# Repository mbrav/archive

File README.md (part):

<h1>api_final</h1>
<p>api final</p>
<h2>Описание проекта: README.md</h2>
<p>Выполненный проект должен сопровождаться описанием.</p>
<ul>
<li>[ ] <strong>Описание</strong>. Что это за проект, какую задачу он решает, в чём его польза;</li>
<li>[ ] <strong>Установка</strong>. Как развернуть проект на локальной машине;</li>
<li>[ ] <strong>Примеры</strong>. Некоторые примеры запросов к API.</li>
</ul>
<h1>api_yatube</h1>
<p>api_yatube</p>
<h1>asciify</h1>
<p>An image uploader that converts colored images into ASCII art</p>
<h3>Instructions</h3>
<ol>
<li>Run <code>npm install</code></li>
<li>Serve <code>node app.js</code></li>
<li>Go to <code>localhost:3000</code> on your browser</li>
</ol>
<h3>Requirements</h3>
<p>The <code>jp2a</code> bash command must be installed on the system</p>
<h1>Extensions of Bias</h1>
<p>A new media art installation connected to the Internet through a Twitter API. A speculation on how media technology is actively shaping our increasingly biased human natures.</p>
<h1>Circularis</h1>
<p>A project that manifests the aesthetics of generative music patterns through the use of Euclidean geometries and mathematical sequences.</p>
<h2>Contexts</h2>
<p><a href="https://aeon.co/essays/soon-we-will-see-chrono-attached-to-every-form-of-medicine">Life in Circadia</a> by Jessa Gamble</p>
<h1>Code2-SP16</h1>
<h2><a href="https://mbrav.github.io/archive/Code2-SP16/">Link to Gallery</a></h2>
<p>Code from Code 2 class at Parsons BFADT</p>
<p><strong>Instructor</strong>: <a href="https://github.com/whoisbma">Bryan Ma</a></p>
<p>Spring 2016</p>
<h1>DataSeek</h1>
<p>Exploring the undefined boundaries of rational and irrational data</p>
<h1>Digital Archeology</h1>
<p>PUDT 3000 Final<br />
May 2017</p>
<h2>Narrative</h2>
<h3>Chapter I: The Cosmic Present-Past</h3>
<p>Whenever we take a glimpse at the night sky, most of us rarely realize that what we are looking at--is history. Whatever we see in the night sky, is a collection of photons that have traveled for thousands and millions of years from their point of origin. The photons coming from Alpha Centauri for example--our closest neighboring stellar system--is already 4.3 years old by the time it reaches our telescopes. When we look at the center of our galaxy, we see light that is 27,000 years old. When we observe Andromeda, our neighboring galaxy, we see light that is 2.5 million years old. Our night sky is filled with the cosmic past, and the gigabytes of data collected by our telescopes. This data has yet to be 'excavated' and reveal a cosmic secret lurking among the data. The sky, can be considered an opaque sediment through which the universe's timeline can be observed. Just by looking at the sky, we become archeologists--engaged in the excavation of the past.</p>
<h3>Chapter II: Primeval Ocean</h3>
<p>Before the cosmos gained the ability to host any sense of history, it resembled a turbulent and chaotic ocean. Nothing made sense in the beginning and there was little space for history. But as time unfolded, structure started to prevail--out of what initially was meaningless and unstructured chaos.</p>
<p>These are a few artifacts that are part of human history which emerged out of their chaotic background.</p>
<h3>Chapter III: Creation of Meaning</h3>
<p>As artifacts become introduced in human history, so is meaning. Objects are valued for their inner qualities and this is what makes history itself meaningful. Each historic artifact possesses its own inner world. It is therefore up to the excavators to choose which tools to use in order to excavate an artifact's past.</p>
<p>But are all tools able to reveal the meaningfulness of an artifact? Can excavation tools account all meaningfulness of its objects, or is there something that excavation tools omit?</p>
<p>Zoom into the artifacts using the MOUSE WHEEL to reveal their inner world.</p>
<h3>Chapter IV: Digitization</h3>
<p>Today, digitization has become the current tool for excavating and revealing the past. By taking radio-telescope readings of the night sky, 3D scans of ancient Egyptian statues along with carbon dating techniques--humans engage in a excavation process that transforms every form of history, into a digitized past--a collection of data.</p>
<p>Data is the holy grail of ordering chaos and transforming it into order. If this is the current trend in archeology, then what does it do to the value of the artifacts?</p>
<h3>Chapter V: Anthropic Artifacts</h3>
<p>When we take a look at archaeologic artifacts, how do we want to treat and consider them? Should we stop digitizing the past, and learn how to appreciate it as something that is beyond mere information, but that of eternal value, humanistic, and infinite? Should we return to worshiping Pharaohs like Ancient Egyptians did, or Egyptians did Zeus, or Romans did Jupiter? Could digitizing the past be the most logical and obvious thing to do?</p>
<h3>Chapter VI: The End</h3>
<p>Take a moment to enjoy these digitized artifacts. Some of these would probably disintegrate after a few millions of years, but maybe their digital replica's would exist for longer. </p>
<h2>Todo</h2>
<h3>General</h3>
<ul>
<li>[x] Draft a Narrative</li>
<li>[x] Get the text captions or speech working</li>
<li>[x] Include the narrative as text or speech</li>
<li>[x] Finish project Description</li>
<li>[x] Make a project title screen, name, date, etc.</li>
<li>[x] Polish Attract Mode</li>
<li>[ ] Finish scenes</li>
<li>[x] Scene 1<ul>
<li>[x] narrative</li>
</ul>
</li>
<li>[x] Scene 2<ul>
<li>[x] narrative</li>
</ul>
</li>
<li>[x] Scene 3<ul>
<li>[x] narrative</li>
</ul>
</li>
<li>[x] Scene 4<ul>
<li>[x] narrative</li>
</ul>
</li>
<li>[x] Scene 5<ul>
<li>[ ] narrative</li>
</ul>
</li>
<li>[x] Scene 6<ul>
<li>[ ] narrative</li>
</ul>
</li>
<li>[ ] Scene 7<ul>
<li>[ ] narrative</li>
</ul>
</li>
<li>[ ] Scene 8<ul>
<li>[ ] narrative</li>
</ul>
</li>
<li>[ ] Scene 9<ul>
<li>[ ] narrative</li>
</ul>
</li>
<li>[ ] Music Setup</li>
<li>[x] Bug Fixing</li>
</ul>
<h3>Visual Stuff and Misc</h3>
<ul>
<li>[ ] Scene transitions</li>
<li>[x] Add new forms of visuals</li>
<li>[ ] Add more 3D models</li>
<li>[ ] Decrease poly count of 3D models if necessary</li>
</ul>
<h3>Other Stuff</h3>
<h2>Endeavour's Guide for the 21st Century</h2>
<p>A project based on on reviving James Cook's geographic discoveries that where made while he was the captain of <em><a href="https://en.wikipedia.org/wiki/HMS_Endeavour">Endeavour</a></em>. The device is capable of displaying the direction it is directed by using three 7 segment displays.</p>
<h3>Showcase</h3>
<p><a href="https://youtu.be/tzNWS7Lbi3c">The Endeavour Test</a> - YouTube video</p>
<p><a href="https://i.imgur.com/okikHWv.jpg">Project Plan</a> - Sketch</p>
<h3>Functions</h3>
<ul>
<li>[x] have an effective segment display driver</li>
<li>[x] shows the heading direction of the magnetometer</li>
<li>[ ] have four functional modes</li>
<li>[x] heading mode</li>
<li>[ ] compass mode</li>
<li>[x] direct mode  </li>
<li>[x] save mode  </li>
<li>[ ] make it low powered to allow the use with batteries.</li>
<li>[ ] designed case</li>
</ul>
<h1>EvictionCity</h1>
<p>A visualization of New York metropolitan area home evictions, gentrification, policing of neighborhoods and other social issues which are constitutive to the social antagonisms that inevitably arise under capitalism.</p>
<ul>
<li>Using <a href="https://threejs.org/">three.js JavaScript 3D Library</a></li>
<li>NYC Open Data <a href="https://data.cityofnewyork.us/City-Government/Evictions/6z8x-wfk4/data">Evictions Dataset</a><ol>
<li>Raw <a href="https://raw.githubusercontent.com/mbrav/EvictionCity/master/js/data/evictions-raw.js">JSON data</a></li>
<li><a href="http://mbrav.com/archive/EvictionCity/utilities/util02/">Geocoding and formatting utility</a> using <a href="https://locationiq.com/">LocationIQ</a> (previously it was possible to do it with Google API until it <a href="https://youtu.be/byGIZ4QIHOM">became expensive</a>)</li>
<li><a href="https://raw.githubusercontent.com/mbrav/EvictionCity/master/js/data/geocoded-data-partial.js">Formatted data</a></li>
</ol>
</li>
</ul>
<h1>FlowingPagoda</h1>
<p><em>A Pagoda that never stops flowing...</em></p>
<p>This project was made for one of my classes. It consists of a Pagoda that grows as the season pass.</p>
<h3>Running It</h3>
<ol>
<li><a href="https://processing.org/download/">Download</a> Processing</li>
<li>Install The Minim Library</li>
<li><a href="https://github.com/mixania/FlowingPagoda/archive/master.zip">Download</a> The Project</li>
<li>Run the sketch</li>
</ol>
<h3>Philosophic Meaning</h3>
<p>According to the project’s philosophy, the world and everything that constitutes it relies on a constant process of rebirth and decay. Each moment is an experience of an individual mind-state such as a thought, a memory, a feeling or a perception. A mind-state arises, exists, and since it is impermanent, it soon ceases, following which the next mind-state arises. Thus the consciousness of a sentient being can be seen as a continuous series of birth and decay of these mind-states. Regardless, rebirth always remains the most persistent among these processes.</p>
<p>As the Pagoda flows through the seasons, it is aware that a day will come when it will no longer stand. Its existence will someday become annihilated, but only for a finite time. After its fall, the process of its rebirth will follow after…</p>
<p>The inspiration for this project was drawn from the movie called <em>Crouching Tiger, Hidden Dragon</em> (2000) directed by a Chinese director Ang Lee who is well know being the director of <em>Life of Pi</em> (2012).</p>
<h3>Functions</h3>
<ul>
<li>There are 4 changing seasons</li>
<li>There are 4 different particles that constantly fall</li>
<li>Bamboos that have different stages of growth</li>
<li>Floating Clouds</li>
<li>The Pagoda grows every year</li>
</ul>
<h3>Planned Additions</h3>
<ul>
<li>Create a process of decay of the Pagoda</li>
<li>Create a Chinese dragon that comes every Chinese New Year</li>
<li>Add wind</li>
<li>Add rain</li>
</ul>
<h3>Stages</h3>

<p>Spring</p>

<p>Summer</p>

<p>Fall</p>

<p>Winter</p>
<h1>backend_community_homework</h1>
<p></p>
<h1>backend_community_homework</h1>
<p></p>
<h1>hw04_tests</h1>
<p></p>
<h1>hw05_final</h1>
<p></p>
<ul>
<li>Неправильно сгруппированы импорты. Посмотри, как это рекомендуется делать в pep8 (порядок групп, разделение пустыми строками и т.д.) Еще можно использовать библиотеку <code>isort</code>. Вот есть <a href="https://simpleisbetterthancomplex.com/packages/2016/10/08/isort.html">статья по настройке</a>. Стоит проверить и поправить по всему проекту<ul>
<li><code>isort . --recursive --check-only</code></li>
<li><code>isort . --recursive</code></li>
</ul>
</li>
</ul>
<p>To dump data:
<code>python manage.py dumpdata app.model_name --indent 4 &gt; fixtures/file_name.json</code></p>
<p>To load data:
<code>python manage.py loaddata fixtures/model_name.json --app app.model_name</code></p>
<h1>hw_python_oop</h1>
<p>Sprint 2. Итоговый проект.</p>
<h1>infORM alpha2</h1>
<p>A Physical Computing and Object Relational Mapping tool</p>
<p><a href="https://vimeo.com/161095259">Video</a> of the project</p>
<p>Project's intent <a href="https://mbrav.github.io/archive/infORM/ProjectIntent.pdf">PDF</a></p>
<h2>Instructions</h2>
<p>add your serial port in <em>script.js</em> on the following line:</p>
<p><code>// connect to Serial
serial.open("/dev/cu.usbmodem819431");</code></p>
<p>if you know what you are doing then do...</p>
<p><code>node node/startserver.js</code></p>
<p>if the server does not start, npm dependencies must be install first</p>
<h2>Technologies used</h2>
<ul>
<li>Software<ul>
<li>A node.js server</li>
<li>p5.js JavaScript library</li>
<li>d3.js JavaScript library</li>
<li>JSON</li>
</ul>
</li>
<li>Hardware<ul>
<li>Teensy 3.1 running at 120 MHz (an Arduino Uno might not have enough space or power)</li>
<li>MPU-6050 Accelerometer</li>
<li>HMC5883 Magnetometer</li>
</ul>
</li>
<li>Arduino Libraries<ul>
<li>I2C Library</li>
<li><a href="https://github.com/bblanchon/ArduinoJson">ArduinoJson</a> - An elegant and efficient JSON library for embedded systems.</li>
<li>Adafruit's <a href="https://github.com/adafruit/Adafruit_Sensor">Sensor Library</a></li>
<li>Adafruit's <a href="https://github.com/adafruit/Adafruit_HMC5883_Unified">HMC5883L Library</a></li>
</ul>
</li>
</ul>
<h2>Changes</h2>
<p><strong>alpha2</strong> - March 31, 2016</p>
<ul>
<li>Implemented MPU-6050's temperature readings</li>
<li>Added the HMC5883 magnetometer to the project</li>
<li>Added magnetometer reads</li>
<li>Added different event triggers for each of the type of readings</li>
<li>Improved the calculation of <em>event significance</em> thanks to the added sensors</li>
</ul>
<p><strong>alpha</strong> - March 28, 2016</p>
<ul>
<li>First release</li>
</ul>
<h1>Infrastructural Utopia Tower (2016)</h1>
<p><strong>A <a href="https://vimeo.com/166409996">Video</a> of the Installation</strong></p>
<h2>Abstract</h2>
<p><em>Infrastructural Utopia Tower</em> is an art installation that emphasizes on the way our modern society has become reliant on infrastructures and automated systems. For a modern human, infrastructure is second nature. Without infrastructure, a human would think he/she had been placed in the wilderness. Us humans, attempt to apply infrastructures almost everywhere while the technological advances only aid this process.</p>
<p>Infrastructure is meant to be built in technological environments. We are affected by it, most of the time without even noticing; hundreds of wires pass through walls, dozens of pipes are laid beneath us, and an unknown number of radio frequencies pass through our bodies. All this illustrates infrastructure’s overwhelming presence, yet, it is cleverly engineered to remain unnoticed. We have the privilege to blindly use the word “working” to describe the thousands of operations that infrastructures perform on a daily basis. This however, is a burden as much as it is considered to be a privilege.
<em>Infrastructural Utopia Tower</em> also emphasizes on government surveillance. Surveillance however, is not made possible without it's underlying framework - infrastructure. When something becomes infrastructuralized, one should not wonder why it can be exploited for someone else's advantage. It is a system designed to remain hidden to its intended user, and nevertheless remain manipulable. Combating surveilance becomes ineffective if one does not realize the implications of its underlying framework on top of which it is built. Infrastructure by definition is meant to be controlled and manipulated, this aspect is frequently overlooked since the root in the word infrastructure, <em>infra</em>  - means closed. The technologies we use on a daily basis is perfect example of how hidden technologies can abstract their intended function.</p>
<p>“Infrastructuralize everything” - is a slogan that is subconsciously ingrained in almost every modern human being. It is a process that has to welcome reflection on our part since the perplexities that arise from it, might not always be apparent. <em>Infrastructural Utopia Tower</em> is an infrastructure, the way it was built reflects this aspect. The way it was realized however, is unlike its intended utopian model. It was meant to stand like its 3D model, manifesting the ideals that have had the potential to be realized. This realization did not happen, and the existence of the ideal did not go beyond a 3D model on an LCD screen. What has been realized however, is an anti-utopian application of infrastructure within the tower. The structure transformed into a breeding ground for humankind to infrastructialize as much estate that nature can provide. The outcome is an anti-utopian looking tower that reflects this human characteristic.</p>
<p>The piece features a Wi-Fi spot that sniffs the user data as he/she browses the internet. This serves as a metaphor that illustrates infrastructure's constant connectedness. The tower’s intention is not to hide the infrastructure away from the user, but show its overwhelming presence, authority, and control. An aspect that infrastructures do not have the possibility to show since they remain constantly hidden.</p>
<p>The tower was meant to proclaim digital freedom, an important tool for maintaining a free democratic society in our present. But digital technologies like the internet, are arguably, one of the most manipulable infrastructures that humankind has every built. Today like never before, someone can control the outcome of something that is located on the other side of the globe, or know everything about the individuals that surround him. We are all part of a grid of infrastructures that provide us with resources, commodities, and sustainable living conditions. Many infrastructures also rely on other infrastructures which translates into us being part of the infrastructural grid as well. Even in the most remote places on Earth, infrastructures consist of satellites that fly above our heads. It sounds more literal than it might appear, but when it comes to infrastructures, humans are never in “offline” mode.</p>
<p>The question that has to be asked is whether infrastructures can be used as means for maintaining freedom. Is there a point where freedom can become instrastructialized given the increase in our reliance on technologies? What is the balance between what should be inrastructuralized, and what should not? If our living conditions can be easily provided by infrastructured means, can freedom eventually be “served” like tap water? Once infrastructures become tools for providing human dependencies in very abstracted ways, would human beings not be blind enough to notice this malicious process? If infrastructures are meant to remain so unnoticeable, what is the truth that they hide? These are questions that must be made by a technologically advancing civilization, especially by its citizens.</p>
<h3>Hardware and Technologies Used</h3>
<ul>
<li>Arduino</li>
<li>openFrameworks running on the Raspberry Pi 3</li>
<li>Serial communication</li>
<li>180 APA102 LED Strips
&lt;&lt;&lt;&lt;&lt;&lt;&lt; HEAD
&lt;&lt;&lt;&lt;&lt;&lt;&lt; HEAD</li>
</ul>
<h1>api_final</h1>
<p>api final</p>
<h2>Описание проекта: README.md</h2>
<p>Выполненный проект должен сопровождаться описанием.</p>
<ul>
<li>[ ] <strong>Описание</strong>. Что это за проект, какую задачу он решает, в чём его польза;</li>
<li>[ ] <strong>Установка</strong>. Как развернуть проект на локальной машине;</li>
<li>[ ] <strong>Примеры</strong>. Некоторые примеры запросов к API.</li>
</ul>
<h1>api_yatube</h1>
<p>api_yatube</p>
<h1>asciify</h1>
<p>An image uploader that converts colored images into ASCII art</p>
<h3>Instructions</h3>
<ol>
<li>Run <code>npm install</code></li>
<li>Serve <code>node app.js</code></li>
<li>Go to <code>localhost:3000</code> on your browser</li>
</ol>
<h3>Requirements</h3>
<p>The <code>jp2a</code> bash command must be installed on the system</p>
<h1>Extensions of Bias</h1>
<p>A new media art installation connected to the Internet through a Twitter API. A speculation on how media technology is actively shaping our increasingly biased human natures.</p>
<h1>Circularis</h1>
<p>A project that manifests the aesthetics of generative music patterns through the use of Euclidean geometries and mathematical sequences.</p>
<h2>Contexts</h2>
<p><a href="https://aeon.co/essays/soon-we-will-see-chrono-attached-to-every-form-of-medicine">Life in Circadia</a> by Jessa Gamble</p>
<h1>Code2-SP16</h1>
<p>Code from Code 2 class at Parsons BFADT</p>
<p><strong>Instructor</strong>: <a href="https://github.com/whoisbma">Bryan Ma</a></p>
<p>Spring 2016</p>
<h1>DataSeek</h1>
<p>Exploring the undefined boundaries of rational and irrational data</p>
<h1>Digital Archeology</h1>
<p>PUDT 3000 Final<br />
May 2017</p>
<h2>Narrative</h2>
<h3>Chapter I: The Cosmic Present-Past</h3>
<p>Whenever we take a glimpse at the night sky, most of us rarely realize that what we are looking at--is history. Whatever we see in the night sky, is a collection of photons that have traveled for thousands and millions of years from their point of origin. The photons coming from Alpha Centauri for example--our closest neighboring stellar system--is already 4.3 years old by the time it reaches our telescopes. When we look at the center of our galaxy, we see light that is 27,000 years old. When we observe Andromeda, our neighboring galaxy, we see light that is 2.5 million years old. Our night sky is filled with the cosmic past, and the gigabytes of data collected by our telescopes. This data has yet to be 'excavated' and reveal a cosmic secret lurking among the data. The sky, can be considered an opaque sediment through which the universe's timeline can be observed. Just by looking at the sky, we become archeologists--engaged in the excavation of the past.</p>
<h3>Chapter II: Primeval Ocean</h3>
<p>Before the cosmos gained the ability to host any sense of history, it resembled a turbulent and chaotic ocean. Nothing made sense in the beginning and there was little space for history. But as time unfolded, structure started to prevail--out of what initially was meaningless and unstructured chaos.</p>
<p>These are a few artifacts that are part of human history which emerged out of their chaotic background.</p>
<h3>Chapter III: Creation of Meaning</h3>
<p>As artifacts become introduced in human history, so is meaning. Objects are valued for their inner qualities and this is what makes history itself meaningful. Each historic artifact possesses its own inner world. It is therefore up to the excavators to choose which tools to use in order to excavate an artifact's past.</p>
<p>But are all tools able to reveal the meaningfulness of an artifact? Can excavation tools account all meaningfulness of its objects, or is there something that excavation tools omit?</p>
<p>Zoom into the artifacts using the MOUSE WHEEL to reveal their inner world.</p>
<h3>Chapter IV: Digitization</h3>
<p>Today, digitization has become the current tool for excavating and revealing the past. By taking radio-telescope readings of the night sky, 3D scans of ancient Egyptian statues along with carbon dating techniques--humans engage in a excavation process that transforms every form of history, into a digitized past--a collection of data.</p>
<p>Data is the holy grail of ordering chaos and transforming it into order. If this is the current trend in archeology, then what does it do to the value of the artifacts?</p>
<h3>Chapter V: Anthropic Artifacts</h3>
<p>When we take a look at archaeologic artifacts, how do we want to treat and consider them? Should we stop digitizing the past, and learn how to appreciate it as something that is beyond mere information, but that of eternal value, humanistic, and infinite? Should we return to worshiping Pharaohs like Ancient Egyptians did, or Egyptians did Zeus, or Romans did Jupiter? Could digitizing the past be the most logical and obvious thing to do?</p>
<h3>Chapter VI: The End</h3>
<p>Take a moment to enjoy these digitized artifacts. Some of these would probably disintegrate after a few millions of years, but maybe their digital replica's would exist for longer. </p>
<h2>Todo</h2>
<h3>General</h3>
<ul>
<li>[x] Draft a Narrative</li>
<li>[x] Get the text captions or speech working</li>
<li>[x] Include the narrative as text or speech</li>
<li>[x] Finish project Description</li>
<li>[x] Make a project title screen, name, date, etc.</li>
<li>[x] Polish Attract Mode</li>
<li>[ ] Finish scenes</li>
<li>[x] Scene 1<ul>
<li>[x] narrative</li>
</ul>
</li>
<li>[x] Scene 2<ul>
<li>[x] narrative</li>
</ul>
</li>
<li>[x] Scene 3<ul>
<li>[x] narrative</li>
</ul>
</li>
<li>[x] Scene 4<ul>
<li>[x] narrative</li>
</ul>
</li>
<li>[x] Scene 5<ul>
<li>[ ] narrative</li>
</ul>
</li>
<li>[x] Scene 6<ul>
<li>[ ] narrative</li>
</ul>
</li>
<li>[ ] Scene 7<ul>
<li>[ ] narrative</li>
</ul>
</li>
<li>[ ] Scene 8<ul>
<li>[ ] narrative</li>
</ul>
</li>
<li>[ ] Scene 9<ul>
<li>[ ] narrative</li>
</ul>
</li>
<li>[ ] Music Setup</li>
<li>[x] Bug Fixing</li>
</ul>
<h3>Visual Stuff and Misc</h3>
<ul>
<li>[ ] Scene transitions</li>
<li>[x] Add new forms of visuals</li>
<li>[ ] Add more 3D models</li>
<li>[ ] Decrease poly count of 3D models if necessary</li>
</ul>
<h3>Other Stuff</h3>
<h2>Endeavour's Guide for the 21st Century</h2>
<p>A project based on on reviving James Cook's geographic discoveries that where made while he was the captain of <em><a href="https://en.wikipedia.org/wiki/HMS_Endeavour">Endeavour</a></em>. The device is capable of displaying the direction it is directed by using three 7 segment displays.</p>
<h3>Showcase</h3>
<p><a href="https://youtu.be/tzNWS7Lbi3c">The Endeavour Test</a> - YouTube video</p>
<p><a href="https://i.imgur.com/okikHWv.jpg">Project Plan</a> - Sketch</p>
<h3>Functions</h3>
<ul>
<li>[x] have an effective segment display driver</li>
<li>[x] shows the heading direction of the magnetometer</li>
<li>[ ] have four functional modes</li>
<li>[x] heading mode</li>
<li>[ ] compass mode</li>
<li>[x] direct mode  </li>
<li>[x] save mode  </li>
<li>[ ] make it low powered to allow the use with batteries.</li>
<li>[ ] designed case</li>
</ul>
<h1>EvictionCity</h1>
<p>A visualization of New York metropolitan area home evictions, gentrification, policing of neighborhoods and other social issues which are constitutive to the social antagonisms that inevitably arise under capitalism.</p>
<ul>
<li>Using <a href="https://threejs.org/">three.js JavaScript 3D Library</a></li>
<li>NYC Open Data <a href="https://data.cityofnewyork.us/City-Government/Evictions/6z8x-wfk4/data">Evictions Dataset</a></li>
<li>Raw <a href="https://raw.githubusercontent.com/mbrav/EvictionCity/master/js/data/evictions-raw.js">JSON data</a></li>
<li><a href="http://mbrav.com/EvictionCity/utilities/util02/">Geocoding and formatting utility</a> using <a href="https://locationiq.com/">LocationIQ</a> (previously it was possible to do it with Google API until it <a href="https://youtu.be/byGIZ4QIHOM">became expensive</a>)</li>
<li><a href="https://raw.githubusercontent.com/mbrav/EvictionCity/master/js/data/geocoded-data-partial.js">Formatted data</a></li>
</ul>
<h1>FlowingPagoda</h1>
<p><em>A Pagoda that never stops flowing...</em></p>
<p>This project was made for one of my classes. It consists of a Pagoda that grows as the season pass.</p>
<h3>Running It</h3>
<ol>
<li><a href="https://processing.org/download/">Download</a> Processing</li>
<li>Install The Minim Library</li>
<li><a href="https://github.com/mixania/FlowingPagoda/archive/master.zip">Download</a> The Project</li>
<li>Run the sketch</li>
</ol>
<h3>Philosophic Meaning</h3>
<p>According to the project’s philosophy, the world and everything that constitutes it relies on a constant process of rebirth and decay. Each moment is an experience of an individual mind-state such as a thought, a memory, a feeling or a perception. A mind-state arises, exists, and since it is impermanent, it soon ceases, following which the next mind-state arises. Thus the consciousness of a sentient being can be seen as a continuous series of birth and decay of these mind-states. Regardless, rebirth always remains the most persistent among these processes.</p>
<p>As the Pagoda flows through the seasons, it is aware that a day will come when it will no longer stand. Its existence will someday become annihilated, but only for a finite time. After its fall, the process of its rebirth will follow after…</p>
<p>The inspiration for this project was drawn from the movie called <em>Crouching Tiger, Hidden Dragon</em> (2000) directed by a Chinese director Ang Lee who is well know being the director of <em>Life of Pi</em> (2012).</p>
<h3>Functions</h3>
<ul>
<li>There are 4 changing seasons</li>
<li>There are 4 different particles that constantly fall</li>
<li>Bamboos that have different stages of growth</li>
<li>Floating Clouds</li>
<li>The Pagoda grows every year</li>
</ul>
<h3>Planned Additions</h3>
<ul>
<li>Create a process of decay of the Pagoda</li>
<li>Create a Chinese dragon that comes every Chinese New Year</li>
<li>Add wind</li>
<li>Add rain</li>
</ul>
<h3>Stages</h3>

<p>Spring</p>

<p>Summer</p>

<p>Fall</p>

<p>Winter</p>
<h1>backend_community_homework</h1>
<p></p>
<h1>backend_community_homework</h1>
<p></p>
<h1>hw04_tests</h1>
<p></p>
<h1>hw05_final</h1>
<p></p>
<ul>
<li>Неправильно сгруппированы импорты. Посмотри, как это рекомендуется делать в pep8 (порядок групп, разделение пустыми строками и т.д.) Еще можно использовать библиотеку <code>isort</code>. Вот есть <a href="https://simpleisbetterthancomplex.com/packages/2016/10/08/isort.html">статья по настройке</a>. Стоит проверить и поправить по всему проекту<ul>
<li><code>isort . --recursive --check-only</code></li>
<li><code>isort . --recursive</code></li>
</ul>
</li>
</ul>
<p>To dump data:
<code>python manage.py dumpdata app.model_name --indent 4 &gt; fixtures/file_name.json</code></p>
<p>To load data:
<code>python manage.py loaddata fixtures/model_name.json --app app.model_name</code></p>
<h1>hw_python_oop</h1>
<p>Sprint 2. Итоговый проект.</p>
<h1>infORM alpha2</h1>
<p>A Physical Computing and Object Relational Mapping tool</p>
<p><a href="https://vimeo.com/161095259">Video</a> of the project</p>
<p>Project's intent <a href="https://github.com/mixania/infORM/blob/master/ProjectIntent.pdf">PDF</a></p>
<h2>Instructions</h2>
<p>add your serial port in <em>script.js</em> on the following line:
<code>// connect to Serial
serial.open("/dev/cu.usbmodem819431");</code></p>
<p>if you know what you are doing then do...
<code>node node/startserver.js</code></p>
<p>if the server does not start, npm dependencies must be install first</p>
<h2>Technologies used</h2>
<ul>
<li>Software</li>
<li>A node.js server</li>
<li>p5.js JavaScript library</li>
<li>d3.js JavaScript library</li>
<li>JSON</li>
<li>Hardware</li>
<li>Teensy 3.1 running at 120 MHz (an Arduino Uno might not have enough space or power)</li>
<li>MPU-6050 Accelerometer</li>
<li>HMC5883 Magnetometer</li>
<li>Arduino Libraries</li>
<li>I2C Library</li>
<li><a href="https://github.com/bblanchon/ArduinoJson">ArduinoJson</a> - An elegant and efficient JSON library for embedded systems.</li>
<li>Adafruit's <a href="https://github.com/adafruit/Adafruit_Sensor">Sensor Library</a></li>
<li>Adafruit's <a href="https://github.com/adafruit/Adafruit_HMC5883_Unified">HMC5883L Library</a></li>
</ul>
<h2>Changes</h2>
<p><strong>alpha2</strong> - March 31, 2016
* Implemented MPU-6050's temperature readings
* Added the HMC5883 magnetometer to the project
* Added magnetometer reads
* Added different event triggers for each of the type of readings
* Improved the calculation of <em>event significance</em> thanks to the added sensors</p>
<p><strong>alpha</strong> - March 28, 2016
* First release</p>
<h1>Infrastructural Utopia Tower (2016)</h1>
<p><strong>A <a href="https://vimeo.com/166409996">Video</a> of the Installation</strong></p>
<h2>Abstract</h2>
<p><em>Infrastructural Utopia Tower</em> is an art installation that emphasizes on the way our modern society has become reliant on infrastructures and automated systems. For a modern human, infrastructure is second nature. Without infrastructure, a human would think he/she had been placed in the wilderness. Us humans, attempt to apply infrastructures almost everywhere while the technological advances only aid this process.</p>
<p>Infrastructure is meant to be built in technological environments. We are affected by it, most of the time without even noticing; hundreds of wires pass through walls, dozens of pipes are laid beneath us, and an unknown number of radio frequencies pass through our bodies. All this illustrates infrastructure’s overwhelming presence, yet, it is cleverly engineered to remain unnoticed. We have the privilege to blindly use the word “working” to describe the thousands of operations that infrastructures perform on a daily basis. This however, is a burden as much as it is considered to be a privilege.
<em>Infrastructural Utopia Tower</em> also emphasizes on government surveillance. Surveillance however, is not made possible without it's underlying framework - infrastructure. When something becomes infrastructuralized, one should not wonder why it can be exploited for someone else's advantage. It is a system designed to remain hidden to its intended user, and nevertheless remain manipulable. Combating surveilance becomes ineffective if one does not realize the implications of its underlying framework on top of which it is built. Infrastructure by definition is meant to be controlled and manipulated, this aspect is frequently overlooked since the root in the word infrastructure, <em>infra</em>  - means closed. The technologies we use on a daily basis is perfect example of how hidden technologies can abstract their intended function.</p>
<p>“Infrastructuralize everything” - is a slogan that is subconsciously ingrained in almost every modern human being. It is a process that has to welcome reflection on our part since the perplexities that arise from it, might not always be apparent. <em>Infrastructural Utopia Tower</em> is an infrastructure, the way it was built reflects this aspect. The way it was realized however, is unlike its intended utopian model. It was meant to stand like its 3D model, manifesting the ideals that have had the potential to be realized. This realization did not happen, and the existence of the ideal did not go beyond a 3D model on an LCD screen. What has been realized however, is an anti-utopian application of infrastructure within the tower. The structure transformed into a breeding ground for humankind to infrastructialize as much estate that nature can provide. The outcome is an anti-utopian looking tower that reflects this human characteristic.</p>
<p>The piece features a Wi-Fi spot that sniffs the user data as he/she browses the internet. This serves as a metaphor that illustrates infrastructure's constant connectedness. The tower’s intention is not to hide the infrastructure away from the user, but show its overwhelming presence, authority, and control. An aspect that infrastructures do not have the possibility to show since they remain constantly hidden.</p>
<p>The tower was meant to proclaim digital freedom, an important tool for maintaining a free democratic society in our present. But digital technologies like the internet, are arguably, one of the most manipulable infrastructures that humankind has every built. Today like never before, someone can control the outcome of something that is located on the other side of the globe, or know everything about the individuals that surround him. We are all part of a grid of infrastructures that provide us with resources, commodities, and sustainable living conditions. Many infrastructures also rely on other infrastructures which translates into us being part of the infrastructural grid as well. Even in the most remote places on Earth, infrastructures consist of satellites that fly above our heads. It sounds more literal than it might appear, but when it comes to infrastructures, humans are never in “offline” mode.</p>
<p>The question that has to be asked is whether infrastructures can be used as means for maintaining freedom. Is there a point where freedom can become instrastructialized given the increase in our reliance on technologies? What is the balance between what should be inrastructuralized, and what should not? If our living conditions can be easily provided by infrastructured means, can freedom eventually be “served” like tap water? Once infrastructures become tools for providing human dependencies in very abstracted ways, would human beings not be blind enough to notice this malicious process? If infrastructures are meant to remain so unnoticeable, what is the truth that they hide? These are questions that must be made by a technologically advancing civilization, especially by its citizens.</p>
<h3>Hardware and Technologies Used</h3>
<ul>
<li>Arduino</li>
<li>openFrameworks running on the Raspberry Pi 3</li>
<li>Serial communication</li>
<li>180 APA102 LED Strips</li>
</ul>
<h1>Core Lab: Systems</h1>
<p><strong>Instructors</strong>: Miri Park &amp; Bryan Collinsworth</p>
<p>Fall 2016</p>
<h2>Sketches</h2>
<h3><a href="02/">02</a> - Random Sequence</h3>

<h3><a href="03/">03</a> - Fibonacci Sequence</h3>

<h3><a href="04/">04</a> - Fibonacci Sequence &amp; Composition</h3>

<h3><a href="05/">05</a> - Chaotic Harmony</h3>

<h3><a href="06/">06</a> - Sleep Harmonics I</h3>

<h3><a href="07/">07</a> - Sleep Harmonics II</h3>

<h3><a href="08/">08</a> - Sleep Harmonics III</h3>

<h3><a href="09/">09</a> - Emancipation from Sleep Data</h3>

<h3><a href="10/">10</a> - Sleep Data Abyss</h3>

<h3><a href="11/">11</a> - Sleep Data Abyss II</h3>

<h3><a href="12/">12</a> - Sleep Data Abyss III</h3>

<h3><a href="13/">13</a> - Ice Nine Unleashed</h3>

<h3><a href="14/">14</a> - Green-Ice Resistance</h3>

<h3><a href="15/">15</a> - Post-Ice Condition</h3>

<h3><a href="16/">16</a> - NYC Graffiti Data</h3>

<h3><a href="17/">17</a> - Glitch Outcomes</h3>

<h3><a href="18/">18</a> - n+1 Dimension</h3>

<h3><a href="19/">19</a> - Data Cocoon</h3>

<h3><a href="20/">20</a> - Sound Data Cocoon</h3>

<h3><a href="21/">21</a> - Data Dystopia</h3>

<h3><a href="22/">22</a> - Data Dystopia II</h3>

<h3><a href="23/">23</a> - Sea Shell</h3>

<h3><a href="24/">24</a> - 4D trigonometry</h3>

<h3><a href="25/">25</a> - 4D trigonometry II</h3>

<h3><a href="26/">26</a> - Polygon Planets</h3>

<h3><a href="27/">27</a> - Time Fabric</h3>

<h3><a href="28/">28</a> - Shadows</h3>

<h3><a href="29/">29</a> - WebGL</h3>

<h1>Lab-SP17</h1>
<p>Code from Lab: Collaboration, Parsons BFADT, Spring 2017</p>
<p><strong>Instructor:</strong> Aaron Lehr</p>
<h3><a href="01/">01</a> - terra-form</h3>
<h3><a href="02/">02</a> - museum-visit</h3>
<h3><a href="03/">03</a> - museum-visualization</h3>
<h3><a href="04/">04</a> - ascii</h3>
<h3><a href="https://github.com/mbrav/asciify">05</a> - ASCIIfy</h3>
<h3><a href="06/">06</a> - Web Scraping</h3>
<h3><a href="07/">07  - Midterm</a> - Wiki Faces</h3>
<h1>Lab-SP17</h1>
<p>Code from Lab: Collaboration, Parsons BFADT, Spring 2017</p>
<p><strong>Instructor:</strong> Aaron Lehr</p>
<h3><a href="01/">01</a> - terra-form</h3>
<h3><a href="02/">02</a> - museum-visit</h3>
<h3><a href="03/">03</a> - museum-visualization</h3>
<h3><a href="04/">04</a> - ascii</h3>
<h3><a href="https://github.com/mbrav/asciify">05</a> - ASCIIfy</h3>
<h3><a href="06/">06</a> - Web Scraping</h3>
<h3><a href="07/">07  - Midterm</a> - Wiki Faces</h3>
<p>test# archive
Archive of my old repos</p>
<h1>Multiverse Clockwork</h1>
<p>An openFrameworks project inspired by Clockwork Orange and nihilistic theoretical physics</p>
<p><a href="https://vimeo.com/164663100">Video</a> of the project</p>
<h2>Concept</h2>
<p>For this creative coding project I wanted imitate the animations that were popular at the time when <em>A Clockwork Orange</em> (1971) was created. During that time, computer graphics first started to emerge. I wanted to create an animation that would encompass the aspects of CG if they were to be applied in the <em>A Clockwork Orange</em> movie, but with the inclusion of a few animations that would convey multiverse theory concepts. The translation of a orange circle came out more literal than the translation of the multiverse concept, this turned out to be in parallel with their comprehensibility. The multiverse theory concepts are influenced by Jim Holt’s book <em>Why Does the World Exist?</em>.</p>
<p>The animation starts with the original <em>A Clockwork Orange</em> theme melody which signifies the low complexity of one universe. This part of the animation is very literal. Then as the music progresses into a more progressive form, the animations become more intricate, abstract, and complex. This is an attempt to convey the complexity of multiverse theories which are abstract to our comprehension as are the animations that try to represent them.</p>
<p>The way this coding project was taking its path easily emerged into such a theme and has yielded pretty satisfying results. The code itself is almost 700 lines long which gives it an ironic aspect; it is written in such a fashion that only its creator can understand.This is similar to the way multiverses can be imagined as ideas since we might not be able to comprehend their inner functioning. The way this project was coded should be a challenge for anyone’s understanding.</p>
<h2>Copyright material</h2>
<p>ClockWork Orange - Funeral Of Queen Mary</p>
<p>© A Clockwork Orange</p>
<p>Deadmau5 - Clockwork</p>
<p>© Songbird 2008</p>
<h2>Installation</h2>
<p>First, make sure you are running the <em>Raspbian</em> or <em>NOOBS</em> OS. After you have your Raspberry Pi up and running, make sure <em>pip</em> the python package manager is installed on your Raspberry Pi. If not type the following in Raspberry Pi's terminal.</p>
<p><code>$ sudo apt-get install python-pip</code><br />
Install <a href="http://flask.pocoo.org/">Flask</a> Python microframework
<code>$ sudo pip install flask</code>
Now you are ready to clone the code from GitHub, type the following
<code>$ git clone https://github.com/mixania/rpi-flask.git</code>
Now type the <code>cd</code> command to open the directory
<code>$ cd rpi-flask/</code>
Run the server as <code>sudo</code>(with root privileges)
<code>$ sudo python switch.py</code>
Your server should be running on http://127.0.0.1:80/
</p>
<h2>Description</h2>
<p><em>Stardust Music Composer</em> is an experiment that emphasizes on interactivity and visualization and combining it with music composition. Current Digital Audio Workstation (DAW) software used for music production by professionals, does not incorporate any aspects of interaction outside of the technical realm. This experimental project seeks to add a visual element to the music production process and combine it with an interactive aspect.</p>
<p>The user interacts with the interface by pressing keys that trigger audio loop samples. As the samples play music loops, the user can open a drum machine sequencer and compose a drum pattern and allowing a musical and a visual performance to be produced at the same time.</p>
<p>The visualization is composed of many particles that act like stardust. When there is a peak in the audio levels, a point of gravity is added in the visualization to which all the particles become attracted to. The user can also click on the visualization and interact with the particles. This is perhaps the most important aspect of the music composition that the experiment seeks to emphasize on. Interaction can be just as important as the process of music composition.</p>
<h2>Instructions</h2>
<ol>
<li><a href="https://processing.org/download/">Download</a> Processing</li>
<li>Install The Minim Library using the library manager in Processing</li>
<li>Download this project</li>
<li>Run the sketch by opening any one of the <em>.pde</em> files and clicking <strong>Run</strong></li>
</ol>
<h2>Copyright Material</h2>
<ul>
<li>Audio sample from Miles Davis's <em>Blue In Green</em></li>
</ul>
<h1>TechnelogicalFeudalism</h1>
<p><em>Surveilance from the time when technology was synonymous with art</em></p>
<h2>Description</h2>
<p>Technelogical Feudalism is a experimentation that explores the ways class societies where controlled before the advent of modern manipulable infrastructures. The mode of control that is explored in this particular experimentation is religion. This peace does not critique religion as a system of believe, rather, the way it is applied in societies.</p>
<p>During he Medieval Ages, which where notorious for various pandemics such such as the Black Death, humanity relied on religion as its biggest hope. Today we see how people rely on technology the same way religions where relied on during medieval ages. Technology could bring us increased life expectancy, an increase quality of life, and happiness - the same way religions where believe to. But when humanity relies on something, there is always room for exploitation, especially if that reliance is appealing to the masses.</p>
<p>This experimentation divides the user into two groups, the Noble, and the Peasant. This is an experience that is intended for multiple users where some interact with the experimentation, and other users watch how they interact on the black canvas. The Noble is able to track the mouse portion and clicks. Multiple windows can be opened to simulate the interaction between multiple people.</p>
<p>The peasant side is given an opportunity to accept religion and is given an semi-interactive environment. On the other side of the user, there is a person who looks at his actions. The very fact that he can monitor the actions of the Peasant, means that he is more manipulable. Religion here, is served as a form of entertainment that also translated into a form of surveilance and establishments of control.</p>
<h2>Navigation</h2>
<h4>User chooses his class</h4>

<h4>Peasant's screen</h4>

<h4>You become noble by claiming an oath</h4>

<h4>The noble can now spy on peasants</h4>

<h1>yogabot</h1>
<p>An instagram bot with a set of methodologies that attempt to steal SMM leads from competitor businesses. </p>
<h2>Todo fixes</h2>
<ul>
<li>[x] Interact with feed function <code>feedinteract()</code></li>
<li>[ ] Interact with likers/folowers of competitors </li>
<li>[ ] Follow function <code>follow()</code></li>
<li>[ ] Unfollow function <code>unfollow()</code>s</li>
</ul>
<p>=======</p>
<h1>New York Data City</h1>
<p>NYDC is a project that explores the conventional aspects of data representation. Data visualization is frequently used to convey information using highly abstracted visual and vocabulary symbols. In some cases, humans can only interpret data only because a symbolic reference is provide along the visualization.</p>
<p>Data visualization can be politicized and manipulated through symbols. It can force the viewer to interpret the data in a very intentional and particular way. The semantic symbols in a data visualization, can sometimes become the most significant factor to dictate the viewer’s interpretation of the data. People frequently use terms like “let data speak for itself” as a substitute to meaningful informational representation. Data can be represented in more abstract forms that may convey its inherit nature and its meaningfulness.</p>
<p><a href="https://mbrav.github.io/nydc/01/index.html">Visual 01</a> - NYC Farmer Markets (<a href="https://data.cityofnewyork.us/Health/New-York-City-Farmers-Markets/j8gx-kc43/data">data source</a>)</p>
<p><a href="https://mbrav.github.io/nydc/02/index.html">Visual 02</a> - NYC Water Complaints (<a href="https://data.cityofnewyork.us/Environment/Water-Quality-complaints/qfe3-6dkn/data">data source</a>)</p>
<p><a href="https://mbrav.github.io/nydc/03/index.html">Visual 03</a> - NYC Greenthumb Community Gardens (<a href="https://data.cityofnewyork.us/Environment/NYC-Greenthumb-Community-Gardens/ajxm-kzmj">data source</a>)</p>
<p><a href="https://mbrav.github.io/nydc/04/index.html">Visual 04</a> - NYC Cool Roof Buildings (<a href="https://data.cityofnewyork.us/Environment/NYC-Cool-Roofs-Buildings/uuxn-wzxe/data">data source</a>)</p>
<p><a href="https://mbrav.github.io/nydc/05/index.html">Visual 05</a> - NYC Food Scrap Drop Of Sites (<a href="https://data.cityofnewyork.us/Environment/Food-Scrap-Drop-Off-Sites/rmmq-46n5/data">data source</a>)</p>
<p><a href="https://mbrav.github.io/nydc/06/index.html">Visual 06</a> - NYC Projects in Construction (<a href="https://nycopendata.socrata.com/Housing-Development/Projects-in-Construction-Map/dzgh-ja44/data">data source</a>)</p>
<p><a href="https://mbrav.github.io/nydc/07/index.html">Visual 07</a> - .nyc Domain Registration by Zip Code (<a href="https://data.cityofnewyork.us/Business/-nyc-Domain-Registrations-by-Zip-Code/ymvu-4x4s/data">data source</a>)</p>
<p><a href="https://mbrav.github.io/nydc/08/index.html">Visual 08</a> - NYC Approved Wholesale Markets (<a href="https://data.cityofnewyork.us/Business/Approved-registrants-in-the-wholesale-markets/sapz-4gsi">data source</a>)</p>
<p><a href="https://mbrav.github.io/nydc/09/index.html">Visual 09</a> - NYC Public Recycling Bins (<a href="https://data.cityofnewyork.us/Environment/Public-Recycling-Bins/sxx4-xhzg/data">data source</a>)</p>
<p><a href="https://mbrav.github.io/nydc/10/index.html">Visual 10</a> - NYC Health and Hospital Corporation (HHC) Facilities (<a href="https://data.cityofnewyork.us/Health/NYC-Health-and-Hospitals-Corporation-Facilities/ymhw-9cz9/data">data source</a>)</p>
<p><a href="https://mbrav.github.io/nydc/11/index.html">Visual 11</a> - NYDC Combined visualization</p>

<h2>Instructions</h2>
<p>Use the <code>W</code>,<code>A</code>,<code>S</code>, and<code>D</code> keys to navigate forwards, left , back, and right.</p>
<p>Use <code>Q</code> and <code>E</code> to rotate the camera.</p>
<p>Use the mouse to stir the direction.</p>
<p><strong>Does not yet support mobile device movement</strong>  </p>
<h2>Process</h2>
<p><a href="https://github.com/mbrav/nydc/tree/master/utils">utils</a> - a set of utilities that where used for geocoding and parsing the data.</p>
<p>The converted data can be <a href="https://github.com/mbrav/nydc/tree/master/data">found here</a> as .js files.</p>
<p>Some of the parts of this project are based on <a href="https://github.com/mbrav/nydc/tree/master/graffiti">graffiti-data</a>.</p>
<p>Geocoding <a href="https://youtu.be/WlM96wBV5nU">NYC Greenthumb Community Gardens</a> using Google's API</p>
<p>Geocoding <a href="https://youtu.be/byGIZ4QIHOM">NYC Farmer Markets</a> using Google's API</p>
<h3>Made with</h3>
<ul>
<li><a href="https://threejs.org/">three.js</a> and WebGL</li>
<li><a href="https://nycopendata.socrata.com/">NYC Open Data</a> </li>
</ul>
<h2>Influence</h2>
<p>Cao Fei's - <a href="https://www.youtube.com/watch?v=9MhfATPZA0g">RMB City</a></p>
<p>Cao Fei's - <a href="https://www.youtube.com/watch?v=5vcR7OkzHkI">China Tracy</a></p>
<blockquote>
<h1>&gt;&gt;&gt;&gt;&gt;&gt; nydc/master</h1>
</blockquote>
<h1>KOS-Scripts</h1>
<p>Various scripts using the <a href="https://github.com/KSP-KOS/KOS">kOS mod</a> for <a href="https://store.steampowered.com/app/220200/Kerbal_Space_Program/">KSP</a> </p>
<blockquote>
<blockquote>
<blockquote>
<blockquote>
<blockquote>
<blockquote>
<blockquote>
<p>KOS-Scripts/master</p>
</blockquote>
</blockquote>
</blockquote>
</blockquote>
</blockquote>
</blockquote>
</blockquote>
<h1>Core Lab: Systems</h1>
<p><strong>Instructors</strong>: Miri Park &amp; Bryan Collinsworth</p>
<p>Fall 2016</p>
<h2>Sketches</h2>
<h3><a href="https://mbrav.github.io/archive/Lab-FA16/02/">02</a> - Random Sequence</h3>

<h3><a href="https://mbrav.github.io/archive/Lab-FA16/03/">03</a> - Fibonacci Sequence</h3>

<h3><a href="https://mbrav.github.io/archive/Lab-FA16/04/">04</a> - Fibonacci Sequence &amp; Composition</h3>

<h3><a href="https://mbrav.github.io/archive/Lab-FA16/05/">05</a> - Chaotic Harmony</h3>

<h3><a href="https://mbrav.github.io/archive/Lab-FA16/06/">06</a> - Sleep Harmonics I</h3>

<h3><a href="https://mbrav.github.io/archive/Lab-FA16/07/">07</a> - Sleep Harmonics II</h3>

<h3><a href="https://mbrav.github.io/archive/Lab-FA16/08/">08</a> - Sleep Harmonics III</h3>

<h3><a href="https://mbrav.github.io/archive/Lab-FA16/09/">09</a> - Emancipation from Sleep Data</h3>

<h3><a href="https://mbrav.github.io/archive/Lab-FA16/10/">10</a> - Sleep Data Abyss</h3>

<h3><a href="https://mbrav.github.io/archive/Lab-FA16/11/">11</a> - Sleep Data Abyss II</h3>

<h3><a href="https://mbrav.github.io/archive/Lab-FA16/12/">12</a> - Sleep Data Abyss III</h3>

<h3><a href="https://mbrav.github.io/archive/Lab-FA16/13/">13</a> - Ice Nine Unleashed</h3>

<h3><a href="https://mbrav.github.io/archive/Lab-FA16/14/">14</a> - Green-Ice Resistance</h3>

<h3><a href="https://mbrav.github.io/archive/Lab-FA16/15/">15</a> - Post-Ice Condition</h3>

<h3><a href="https://mbrav.github.io/archive/Lab-FA16/16/">16</a> - NYC Graffiti Data</h3>

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
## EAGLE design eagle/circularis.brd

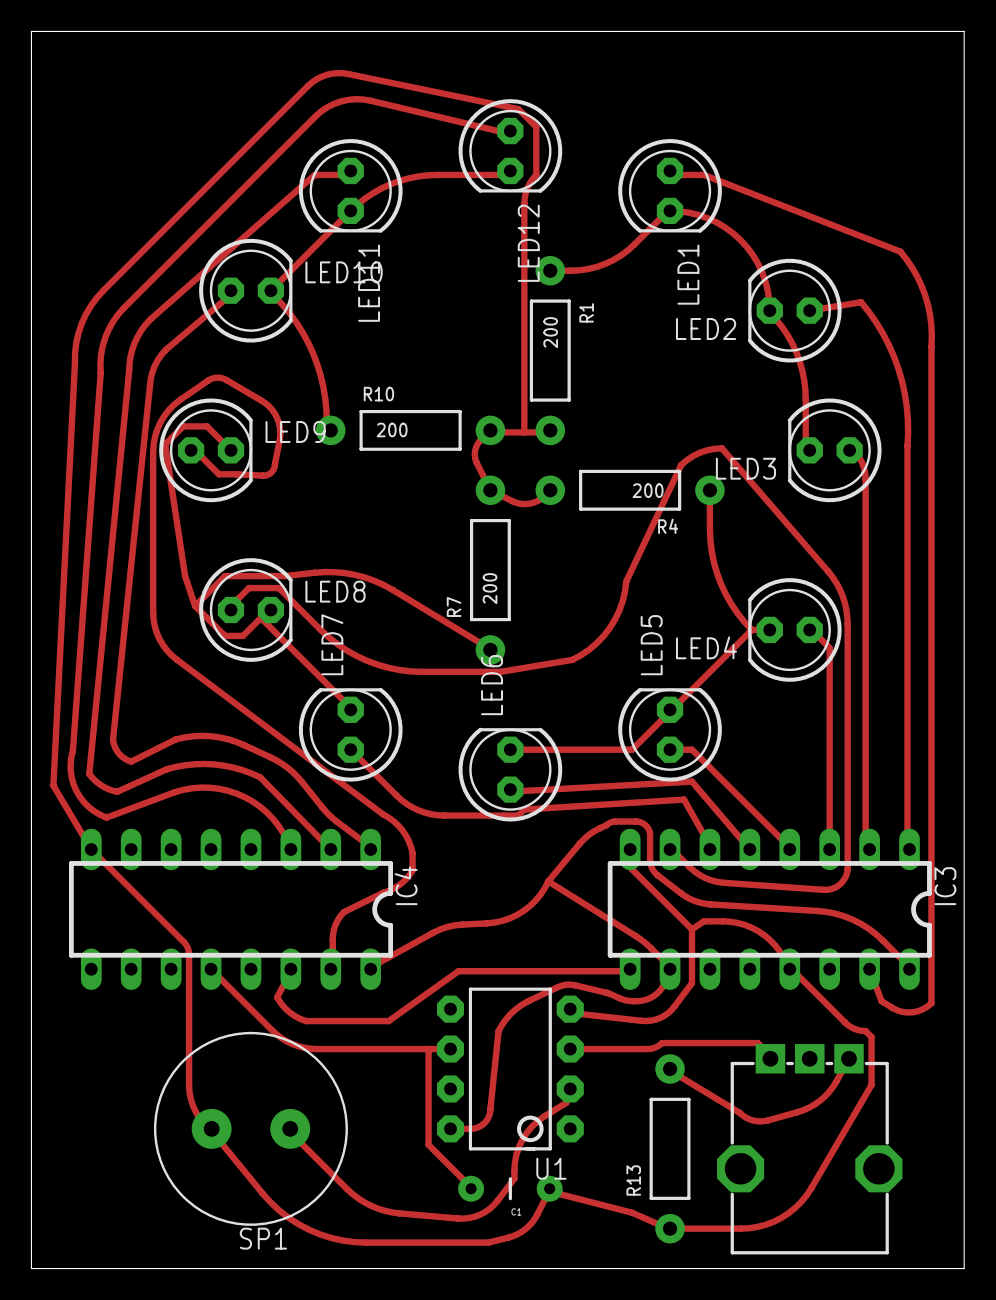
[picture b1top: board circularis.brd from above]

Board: 2 copper layers, 59.4 x 78.7 mm, 23 parts (0 on the bottom side), 23 nets.

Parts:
C1: 1 uf; CAP-PTH-5MM
IC3, IC4: 74LS595N; DIL16
LED1, LED2, LED3, LED4, LED5, LED6, LED7, LED8, LED9, LED10, LED11, LED12: LED5MM
R1, R4, R7, R10: 200; AXIAL-0.4
R13: AXIAL-0.4
RV2: ALPS_POT
SP1: SPEAKER/PS12; PS12
U1: TINY85-20-DIP; DIP08

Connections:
GND: C1.1, IC3.8, IC3.13, IC4.8, R1.P$2, R4.P$2, R7.P$2, R10.P$2, R13.P$1, SP1.P$2, U1.4
unnamed: LED1.K, LED2.K, LED3.K, R1.P$1
unnamed: IC3.9, IC4.14
unnamed: IC3.10, IC3.16, IC4.16, U1.8
unnamed: LED4.K, LED5.K, LED6.K, R4.P$1
unnamed: C1.2, IC4.12, U1.6
unnamed: LED7.K, LED8.K, LED9.K, R7.P$1
unnamed: IC3.1, LED2.A
unnamed: IC3.2, LED3.A
unnamed: IC3.3, LED4.A
unnamed: IC3.4, LED5.A
unnamed: IC3.5, LED6.A
unnamed: IC3.6, LED7.A
unnamed: IC3.15, LED1.A
unnamed: R13.P$2, RV2.P$1
unnamed: RV2.P$3, U1.3
unnamed: IC4.3, LED12.A
unnamed: IC3.7, LED8.A
unnamed: IC4.15, LED9.A
unnamed: IC4.1, LED10.A
unnamed: IC4.2, LED11.A
unnamed: SP1.P$1, U1.2
unnamed: LED10.K, LED11.K, LED12.K, R10.P$1

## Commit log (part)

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2016-03-28 iAdded instructions
2016-03-28 Added millis() timers, re-organized code
2016-03-28 Improved the way eventSignificance is calculated
2016-03-28 Limited the frequency of triggering events
2016-03-28 Added millis() and fps() to the JSON
2016-03-28 Text based on received data is sucesfully drawn
2016-03-28 Event info shows on mousOver
2016-03-29 alpha
2016-03-31 Added a Magnetomer, renamed project to "infORM"
    * renamed the project to "infORM" in order to make a distinction between my other project called "in.fORM" which does manipulation mostley based on text. This project does manipulation based on data 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
2016-03-31 Added seprate event triggeres for each sensors
2016-03-31 implemented temperature readings
2016-03-31 Fixed the 0's in Temp statisitcs, + more comments
2016-03-31 alpha2
    * Implemented MPU-6050's temperature readings
    * Added the HMC5883 magnetometer to the project
    * Added magnetometer reads
    * Added different event triggers for each of the type of readings
    * Improved the calculation of event significance thanks to the added sensors
2016-03-31 Trimmed some values, LED blinks during an event
2016-03-31 Added a video link to README
2016-04-08 Added project's intention pdf
2016-04-08 Added link to PDF
2016-04-08 Fixx README
2016-04-08 Update Philosophic Statement
2016-04-11 Unicorn's tears
    One pixel moving down the strip
2016-04-11 Trailing Unicorn's tear
    One pixel with a tail, fading in 3 pixels
2016-04-11 Passive Agressive Unicron Tears
    One pixel with a tail, fading in 4 pixels and bouncing back to start
2016-04-11 Unicorn is mad because it only has 4.25 colors
    One pixel with a tail, fading in 3 pixels and changing color halfway through
2016-04-11 Unicorn is infuriated and confused
2016-04-11 Unicorn dancess in the purple rain
    A blue color which has a random dripping water effect for 3 seconds (interpretative)
2016-04-12 Unicorn likeis Paparazi
2016-04-12 Did u hear the Furious Unicron Thunder last night?
    One color which lights the whole strip in various colors for .5 second in a in a lightening
    effect (interpretative)
2016-05-06 Initial Setup
    * Arduino now can accept bytes and toggle animations based on that
    * OF sketch pings the Arduino but does nto get response back, will stempt to make it send bytes
    * to the arduino<F6>
2016-05-06 Added 3D models
2016-05-06 Works with bytes converted into ASCII values
2016-05-06 Now can send bytes as numbers
2016-05-06 Added another animation
2016-05-10 .gitignore for rpi
2016-05-10 Added more animations and animation functions
2016-05-10 Fix, puts into serial reading mode
2016-05-10 added aditional patern to Of
2016-05-12 Added texts to OF sketch
2016-05-12 testing sniffer
2016-05-13 added video, sound does not work
2016-05-13 Working movie with text
2016-05-13 changed text
2016-05-13 Fixes in text and video
2016-05-13 animation now is timed to frames rather than time
2016-05-13 typo
2016-05-21 Added README
2016-05-21 year
2016-05-23 without The
2016-06-07 Added schematic to README
2016-06-16 Clarifies on the README
2016-07-03 Added MIT liscense
2016-07-04 Updated the project's intention
2016-07-15 link fix
2016-08-07 project organization
2016-08-07 Added image
2016-08-07 uh, these typos
2016-10-15 Added files
2016-10-15 Edward Snowden vs NSA test
2016-10-15 cool canavs example
2016-10-15 A realm of data personalities, in color
2016-10-15 01 - working version
2016-10-16 client serve cleanup
2016-10-16 Multiplayer three.js interaction - working test
2016-10-16 spheres
2016-10-17 Color BOUALLS!
2016-10-17 Fixed flickering and server reconnect crash bug
2016-10-18 Adding projects, history re-write
2016-10-18 smooth-operator.mp3
2016-10-20 tidy up
2016-10-20 sun of vertices
2016-10-20 bla bla
2016-10-21 Ice Nine
2016-10-21 re-arragnement
2016-10-22 trigonometry
2016-10-23 polygon planets
2016-10-25 help
2016-10-25 02 - water complaints data, parsed with util03
2016-10-25 util fix
2016-10-25 03 - NYC Greenthumb Community Gardens
2016-10-25 04 - NYC Cool Roof Buildings
2016-10-26 05 - NYC Food Scrap Drop Off Sites
2016-10-26 06 - NYC Projects in Construction
2016-10-26 07 - .nyc Domain Registrations by Zip Code
2016-10-26 08 - NYC Approved Wholesale Markets
2016-10-26 09 - NYC Public Recycling Bins
2016-10-27 10 -Health and Hospitals Corporation (HHC) Facilities
2016-10-27 Colors and forms
2016-10-27 hospital signs
2016-10-27 tweaks
2016-10-27 expandable data sets
2016-10-27 4 data sets combined
2016-10-27 5 data sets combined
2016-10-27 6 data sets combined
2016-10-27 6 data sets combined + animations
2016-10-27 8 data sets combined + animations
2016-10-27 9 data sets combined + animations
2016-10-27 10 data sets combined + animations
2016-10-27 README
2016-10-27 formating
2016-10-27 added stement and renamed
2016-10-27 corrected mistakes
2016-11-03 Added instructions
2016-11-03 made with..
2016-11-03 Create master branch via GitHub
2016-11-04 working sequencing melody
2016-11-05 Sequencing light working for the first 8 LED's
2016-11-05 Added eagle files
2016-11-07 glitch art
2016-11-07 number of clints logged to console
2016-11-07 emails containingh criminal records scraped, <3 Hillary
2016-11-07 site fade based on users online
2016-11-07 Contexts
2016-11-08 spoof
2016-11-10 styled spoof
2016-11-13 chat history a bit
2016-12-15 library update
2016-12-27 added img and list
2017-01-14 added studd
2017-01-14 missed some css files
2017-02-15 added mouse rotation controls
2017-02-16 white background
2017-02-16 added visualization
2017-02-16 added image, added ascii
2017-02-16 adding files
2017-02-16 added uploads folder
2017-02-16 added ascci folder
2017-02-16 added verbose output
2017-02-16 bg color
2017-02-21 added links
2017-02-21 added asciffy as 05/
2017-02-21 fixed link
2017-02-24 new projects
2017-02-28 wiki scrape
2017-03-02 wiki mathematicians
2017-03-02 wiki faces scrapes, new files
2017-03-13 wiki faces visualization - beta
2017-03-13 got selection working
2017-03-14 Added image portraits
2017-03-15 fix link
2017-03-15 sadfas
2017-03-16 edits to readme
2017-03-30 node scrape
2017-04-03 box img
2017-04-10 img gallery sorting 3D
2017-04-10 sorting working
2017-04-11 polish
2017-04-12 yea BRoo
2017-04-27 model tower
2017-04-27 loading models named in order
2017-04-27 renamed models[], fixed color, simplified GL part
    - will try to color the models now
2017-04-27 Colorful vertices
2017-04-27 displaced the models, perfect
2017-04-27 Manipulating vertices
2017-05-01 Yumeng's Thesis, I found a meaning in my life on the last day before the end of the world. Skateboards.
2017-05-01 wrapped model into a class
2017-05-02 contrasting colors
2017-05-04 vid1
2017-05-04 rotate and postion matrix
2017-05-04 moving orbit
2017-05-04 text
2017-05-08 made scenes
2017-05-08 colorful scene 3
2017-05-08 shader
2017-05-09 prep
2017-05-09 djfglsdjfg, venus shader add
2017-05-09 got one of my shaders working! Holy F. S.
2017-05-09 shader into models, safasdfas d
2017-05-11 dsfgsdf
2017-05-12 scene control done
2017-05-12 beautify files
2017-05-12 run scene setup in ofApp:update()
2017-05-12 fix caption fromating, looks better now
2017-05-12 todo list, scene work
2017-05-12 ofx profiler
2017-05-12 added new shaders
2017-05-12 star shader
2017-05-13 intro title
2017-05-13 title screen
2017-05-13 space
2017-05-13 added addon
2017-05-13 unresponsive fix attmept
2017-05-13 title fix
2017-05-13 added scene 5, fixed unresponsive bug
2017-05-13 4 chapters ready 4 chapters ready 4 chapters ready 4 chapters ready
2019-09-13 link update
2019-09-13 edit
2019-09-19 aded organizer
2019-10-18 graffiti data
2019-10-25 Initial commit, added a working three.js particle sketch
2019-10-25 added test data
2019-10-27 added data utilities, raytracer
2019-10-27 gathering geolocation...
2019-10-30 displaying 3466 cordinates, collecting more
2019-10-31 working raycaster, still need to add data to particle objects
2019-11-01 Hover over data working, seems like dots correlate with their data
2019-11-01 resembling NYC now
2019-11-01 finding avg values
2019-11-01 more data with 13388 points
2019-11-01 added Eviction City
2019-11-03 added scripts
2019-11-05 implemented orbit controls
2019-11-06 rotation controls implemented, but data is inverted :/
2019-11-06 fixed rotation issue
2019-11-07 26602 data points
2019-11-07 added better CSS styling
2019-11-08 edited description
2019-11-13 35110 data points
2019-11-14 41637 data points
2020-08-26 tets
2020-08-26 url fix
2020-10-11 you aint gettin' my keys bruh
2020-10-12 cleanup
2020-10-12 keys
2020-10-12 add tg_msg function
2020-10-13 like feed
2021-07-01 Скелет
2021-07-01 Record.__init__ test passed
2021-07-01 TestCalculator::test_init PASSED
2021-07-01 TestCalculator::test_add_record PASSED
2021-07-01 Скелет 2.0
2021-07-01 TestCalculator::test_get_today_stats PASSED
2021-07-01 TestCaloriesCalculator::test_init PASSED
2021-07-01 Currency request fix
2021-07-01 test_get_calories_remained PASSED
2021-07-02 TestCashCalculator::test_init
2021-07-02 test_get_today_cash_remained FAILED :/
2021-07-03 test_get_today_cash_remained[0-usd] PASSED
2021-07-03 new remainder
2021-07-03 100% PASS, SUBMIT
2021-07-07 datetime fix
2021-07-07 today_remained func
2021-07-07 currency dict improvement
2021-07-07 __name__ fix
2021-07-07 SUBMIT v2.0
2021-07-09 pytest update
2021-07-10 pytest update 2
2021-07-15 project init
2021-07-15 views config
2021-07-15 static add
2021-07-15 test pass
2021-07-19 fix2
2021-08-12 add files, tests init
2021-08-12 add migrations, fixed a few tests
2021-08-13 url config for new tmeplates
2021-08-13 template organization
2021-08-15 urls and template rework
2021-08-15 added paginator
2021-08-15 test 75% passed
2021-08-15 test 95% passed
2021-08-16 100%
2021-08-16 pep8
2021-08-17 added django-debug-toolbar
2021-08-17 query optimization with select_related()
2021-08-17 template format
2021-08-17 get_object_or_404() with select_related()
2021-08-17 auth config
2021-08-17 form fix
2021-08-18 signup/login forms fix
2021-08-22 test + help-texts
2021-08-22 yatube import
2021-08-22 urls and views tests
2021-08-23 all test except forms
2021-08-23 rollback to satisfy pytest, added about tests
2021-08-23 post create test
2021-08-23 revision 2
2021-08-24 if view fix
2021-08-24 hw04 sync
2021-08-25 added requirments
2021-10-02 7.View-классы API - Урок 2
2021-10-02 7.View-классы API - Урок 3
2021-10-02 8.Вьюсеты и роутеры - Задача 1
2021-10-03 9.Сериализаторы для связанных моделей 1/2
2021-10-03 9.Сериализаторы для связанных моделей 2/2
2021-10-03 10.Сериализаторы: дополнительные настройки - 1/2
2021-10-08 13.Аутентификация по токену. JWT + Djoser 1/1
2021-10-08 move into seperate project before merge with api_yatube
2021-10-08 remove theory
2021-10-08 init
2021-10-08 Add Post, Group and Comment ViewSets
2021-10-09 comment serialer under post
2021-10-09 14/26 tests passed
2021-10-10 18/26, post tests done
2021-10-11 23/26
2021-10-11 25/26
2021-10-11 100% tests
2021-10-12 review edits
2021-10-13 perform_create
2021-10-13 404 object
2021-10-16 project setup
2021-10-18 posts api done
2021-10-18 static files conf
2021-10-20 djoser, 60% tests done
2021-10-24 23/33
2021-10-24 fix permisions
2021-10-24 fic router
2021-10-24 31/33 comment fix
2021-10-24 100%!!!!!
2021-10-24 линт
2021-10-24 unused fix
2021-10-24 build fail fix?
2021-10-25 isort
2021-10-25 http_method_names
2021-11-12 Add mafia-flocking
2021-11-12 Add dope cube
2021-11-12 Add unicorn
2021-11-12 Add EndeavoursGuide
2021-11-12 MultiverseClockwork
2021-11-12 move MultiverseClockwork
2021-11-12 Add what-is-what
2021-11-12 FlowingPagoda
2021-11-12 Add FlowingPagoda
2021-11-12 Add rpi-flask
2021-11-12 Add space-splosion
2021-11-12 Add pong
2021-11-12 Add gravity
2021-11-12 Add InfrastructuralUtopiaTower
2021-11-12 Add TechnelogicalFeudalism
2021-11-12 Add Circularis
2021-11-12 Add Code2-SP16
2021-11-12 Add DigitalArchaeology
2021-11-12 Add DataSeek
2021-11-12 Add 2019.js
2021-11-12 Add EvictionCity
2021-11-12 Add Lab-SP17
2021-11-12 Add Lab-FA16
2021-11-12 Add hw_python_oop
2021-11-12 Add hw02_community
2021-11-12 Add hw03_forms
2021-11-12 Add hw04_tests
2021-11-13 Add hw05_final
2021-11-13 Add api_yatube-master
2021-11-13 Add asciify
2021-11-13 Add yogabot
2021-11-13 Add StardustComposer
2021-11-13 Add README gen script
2021-11-13 generate README
2021-11-19 url fixes
2021-12-17 img test

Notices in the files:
README.md:
© A Clockwork Orange
© Songbird 2008
Copyright Material
parts and their libraries:
SparkFun-DigitalIC: Licensing: Creative Commons ShareAlike 4.0 International - https://creativecommons.org/licenses/by-sa/4.0
